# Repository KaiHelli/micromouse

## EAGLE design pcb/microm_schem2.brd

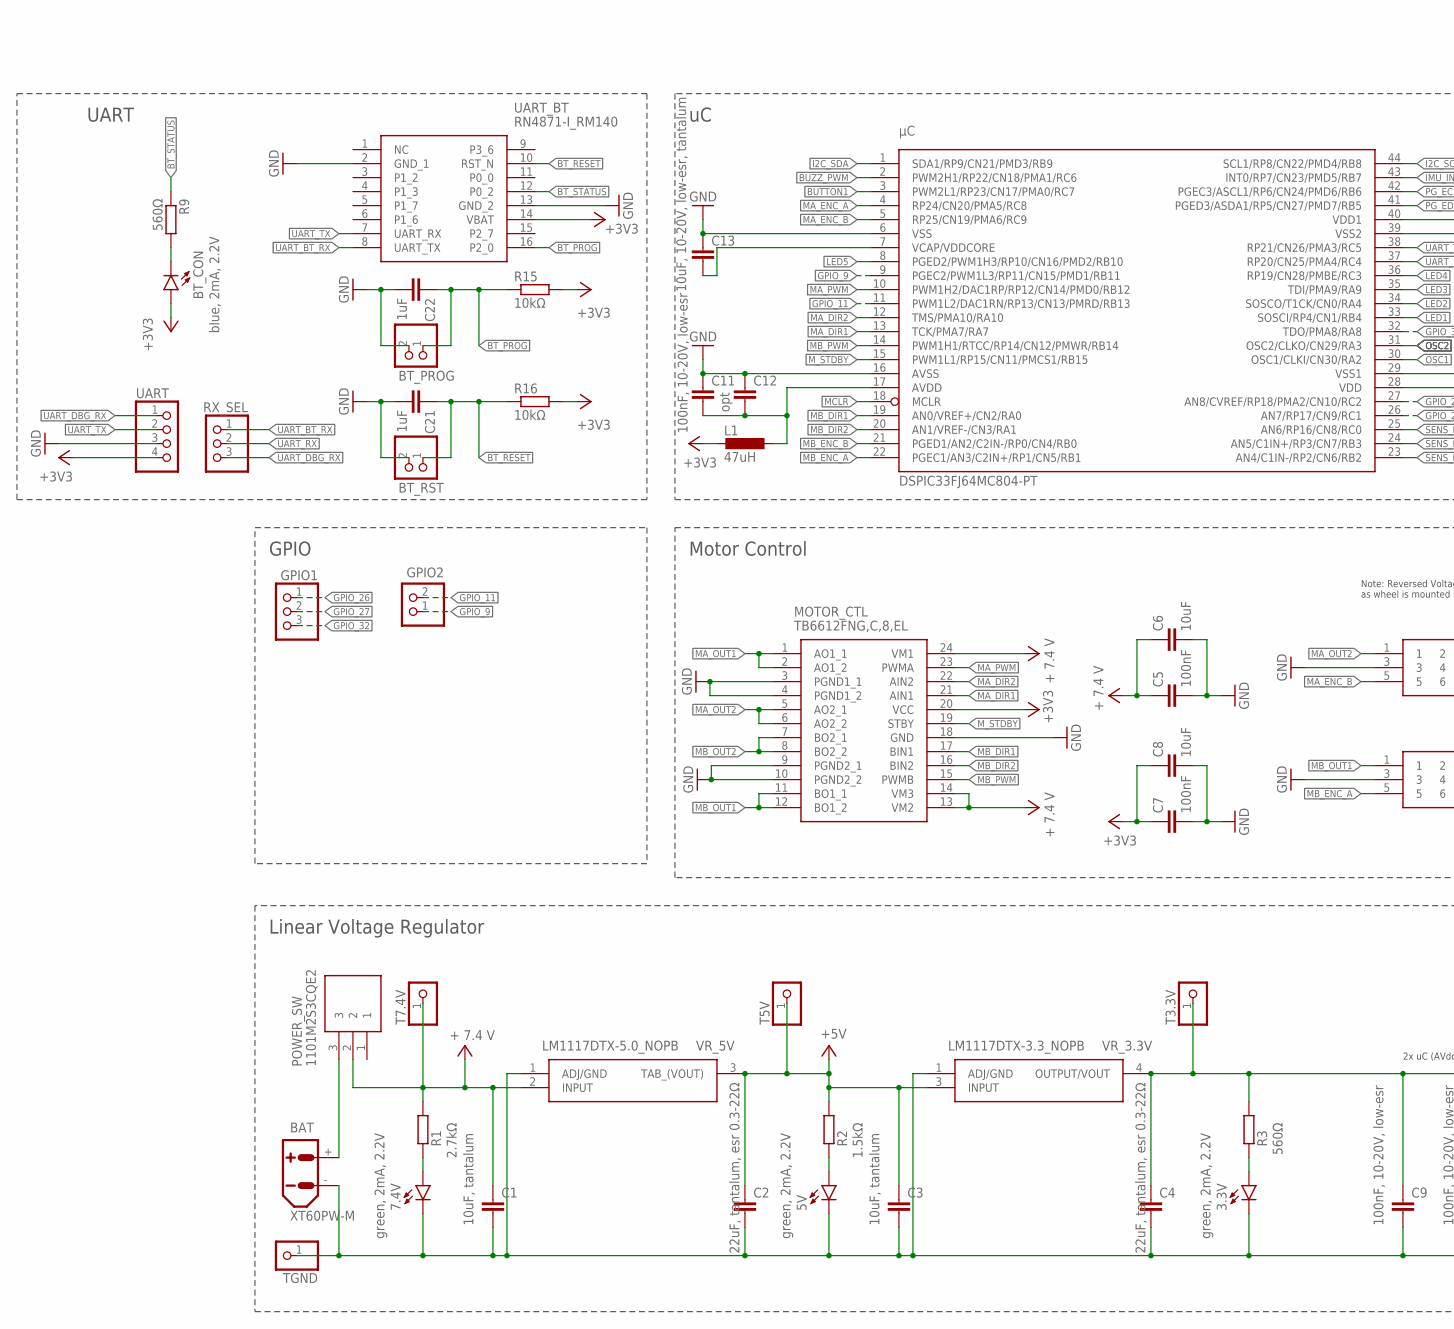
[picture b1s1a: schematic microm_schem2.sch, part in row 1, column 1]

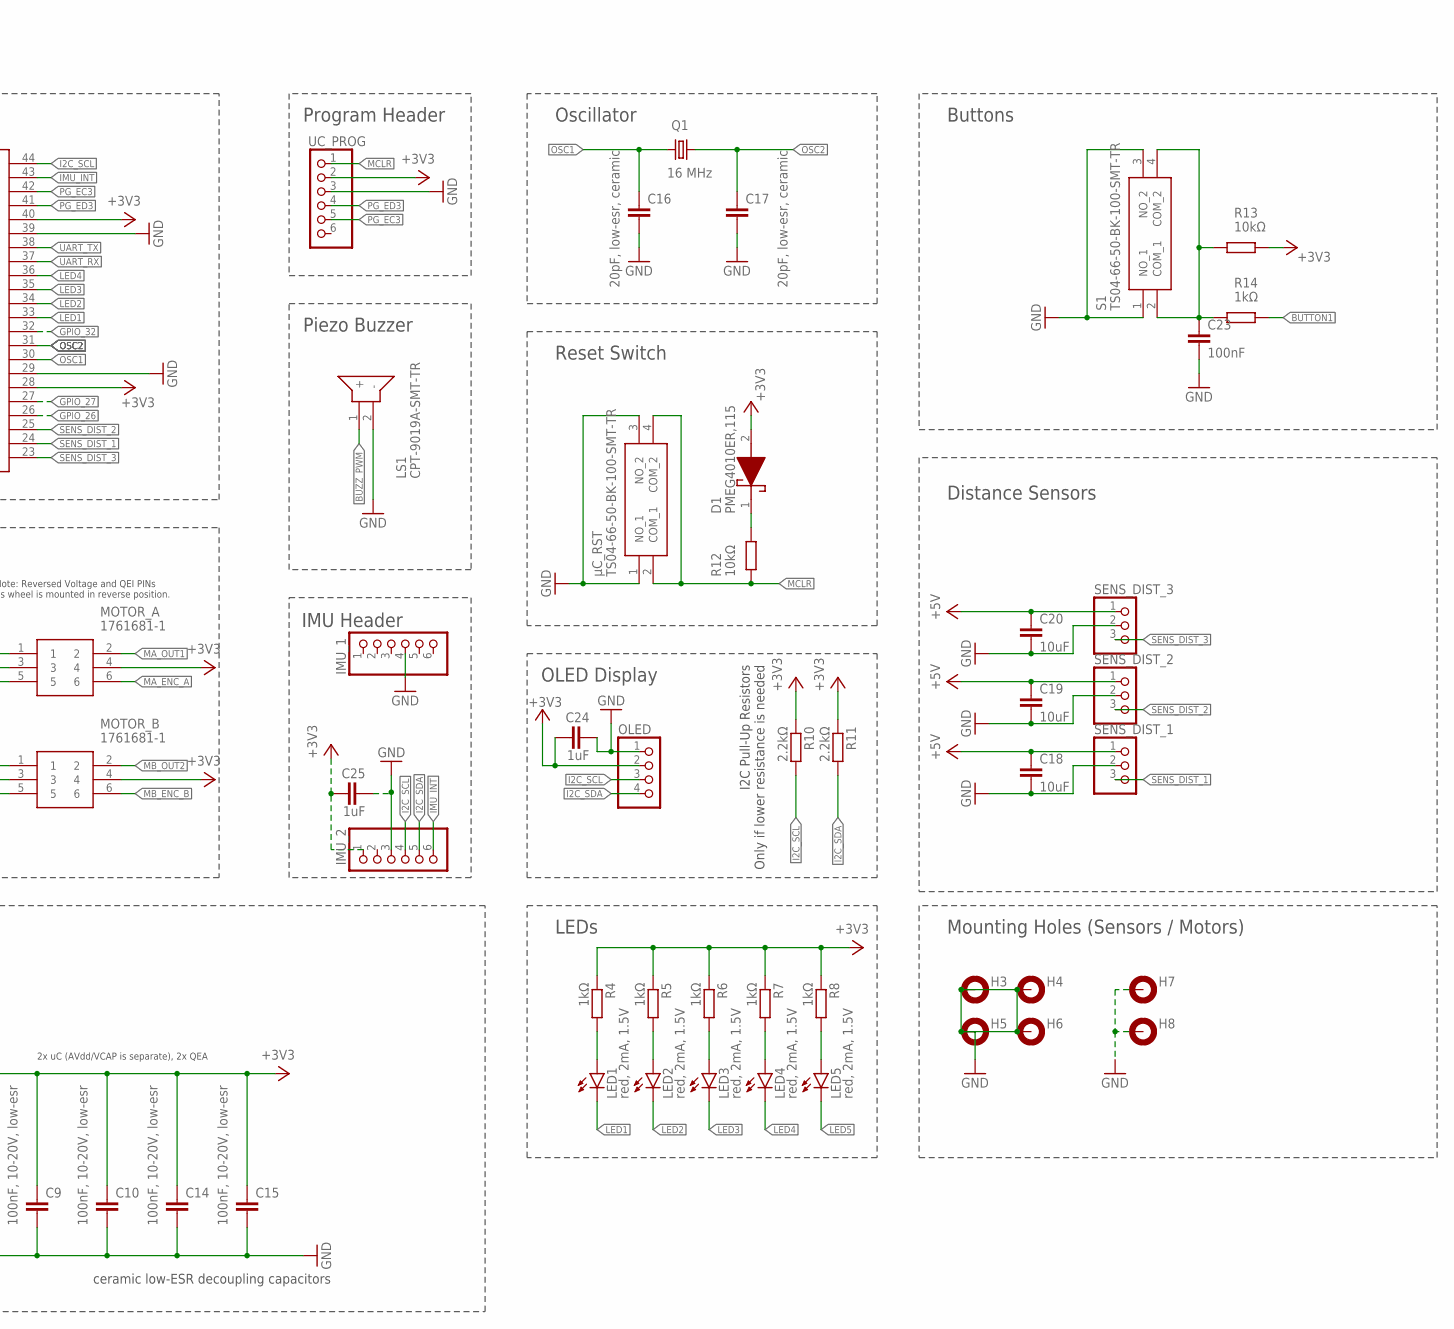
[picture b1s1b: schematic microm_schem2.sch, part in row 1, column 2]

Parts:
3.3V, 5V, 7.4V: green, 2mA, 2.2V; CHIP-LED0805
BAT: XT60PW-M
BT_CON: blue, 2mA, 2.2V; CHIP-LED0805
BT_PROG: PINHD-1X2; 1X02
BT_RST: PINHD-1X2; 1X02
C1, C3: 10uF, tantalum; C0805
C2, C4: 22uF, tantalum, esr 0.3-22Ω; C0805
C5, C7, C23: 100nF; C0805
C6, C8, C18, C19, C20: 10uF; C0805
C9, C10, C11, C14, C15: 100nF, 10-20V, low-esr; C0805
C12: opt; C0805
C13: 10uF, 10-20V, low-esr, tantalum; C0805
C16, C17: 20pF, low-esr, ceramic; C0805
C21, C22, C24, C25: 1uF; C0805
D1: PMEG4010ER,115; PMEG4010ER115
GPIO1: PINHD-1X3; 1X03
GPIO2: PINHD-1X2; 1X02
H3, H4, H5, H6, H7, H8: MOUNT-PAD-ROUND2.8; 2,8-PAD
IMU_1, IMU_2: PINHD-1X6; 1X06
L1: 47uH; L1812
LED1, LED2, LED3, LED4, LED5: red, 2mA, 1.5V; CHIPLED_0805
LS1: CPT-9019A-SMT-TR; CPT9019ASMTTR
MOTOR_A: 1761681-1; SHDR6W67P254_2X3_1524X916X922P
MOTOR_B: 1761681-1; SHDR6W67P254_2X3_1524X916X922P
MOTOR_CTL: TB6612FNG,C,8,EL; SOP65P760X160-24N
OLED: PINHD-1X4; 1X04
POWER_SW: 1101M2S3CQE2; 1000-SERIES(SPDT)
Q1: 16 MHz; HC49/S
R1: 2.7kΩ; R0805
R2: 1.5kΩ; R0805
R3, R9: 560Ω; R0805
R4, R5, R6, R7, R8, R14: 1kΩ; R0805
R10, R11: 2.2kΩ; R0805
R12, R13, R15, R16: 10kΩ; R0805
RX_SEL: PINHD-1X3; 1X03
S1: TS04-66-50-BK-100-SMT-TR; TS046650BK100SMTTR
SENS_DIST_1, SENS_DIST_2, SENS_DIST_3: PINHD-1X3; 1X03
T3.3V, T5V, T7.4V: PINHD-1X1; 1X01
TGND: PINHD-1X1; 1X01
UART: PINHD-1X4; 1X04
UART_BT: RN4871-I_RM140; RN4871IRM140
UC_PROG: PINHD-1X6; 1X06
VR_3.3V: LM1117DTX-3.3_NOPB; LM1117DTX33NOPB
VR_5V: LM1117DTX-5.0_NOPB; LM78M05CDT
µC_RST: TS04-66-50-BK-100-SMT-TR; TS046650BK100SMTTR
μC: DSPIC33FJ64MC804-PT; TQFP44

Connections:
+3V3: BT_CON.A, C4.1, C7.1, C8.1, C9.1, C10.1, C14.1, C15.1, C24.1, C25.1, D1.2 (A), IMU_2.1, L1.2, MOTOR_A.4, MOTOR_B.4, MOTOR_CTL.20 (VCC), OLED.2, R3.1, R4.1, R5.1, R6.1, R7.1, R8.1, R10.1, R11.1, R13.2, R15.2, R16.2, T3.3V.1, UART.4, UART_BT.14 (VBAT), UC_PROG.2, VR_3.3V.4 (OUTPUT/VOUT), μC.28 (VDD), μC.40 (VDD1)
+5V: C2.1, C3.1, C18.1, C19.1, C20.1, R2.1, SENS_DIST_1.1, SENS_DIST_2.1, SENS_DIST_3.1, T5V.1, VR_3.3V.3 (INPUT), VR_5V.3 (TAB_(VOUT))
+7V4: C1.1, C5.1, C6.1, MOTOR_CTL.13 (VM2), MOTOR_CTL.14 (VM3), MOTOR_CTL.24 (VM1), POWER_SW.2, R1.1, T7.4V.1, VR_5V.2 (INPUT)
BT_PROG: BT_PROG.1, C22.1, R15.1, UART_BT.16 (P2_0)
BT_RESET: BT_RST.1, C21.1, R16.1, UART_BT.10 (RST_N)
BT_STATUS: R9.1, UART_BT.12 (P0_2)
BUTTON1: R14.2, μC.3 (PWM2L1/RP23/CN17/PMA0/RC7)
BUZZ_PWM: LS1.1 (+), μC.2 (PWM2H1/RP22/CN18/PMA1/RC6)
GND: 3.3V.C, 5V.C, 7.4V.C, BAT.-, BT_PROG.2, BT_RST.2, C1.2, C2.2, C3.2, C4.2, C5.2, C6.2, C7.2, C8.2, C9.2, C10.2, C11.1, C12.1, C13.1, C14.2, C15.2, C16.2, C17.2, C18.2, C19.2, C20.2, C21.2, C22.2, C23.2, C24.2, C25.2, H3.B2,8, H4.B2,8, H5.B2,8, H6.B2,8, H7.B2,8, H8.B2,8, IMU_1.4, IMU_2.3, LS1.2 (-), MOTOR_A.3, MOTOR_B.3, MOTOR_CTL.3 (PGND1_1), MOTOR_CTL.4 (PGND1_2), MOTOR_CTL.9 (PGND2_1), MOTOR_CTL.10 (PGND2_2), MOTOR_CTL.18 (GND), OLED.1, S1.1 (NO_1), S1.3 (NO_2), SENS_DIST_1.2, SENS_DIST_2.2, SENS_DIST_3.2, TGND.1, UART.3, UART_BT.2 (GND_1), UART_BT.13 (GND_2), UC_PROG.3, VR_3.3V.1 (ADJ/GND), VR_5V.1 (ADJ/GND), µC_RST.1 (NO_1), µC_RST.3 (NO_2), μC.6 (VSS), μC.16 (AVSS), μC.29 (VSS1), μC.39 (VSS2)
GPIO_9: GPIO2.1, μC.9 (PGEC2/PWM1L3/RP11/CN15/PMD1/RB11)
GPIO_11: GPIO2.2, μC.11 (PWM1L2/DAC1RN/RP13/CN13/PMRD/RB13)
GPIO_26: GPIO1.1, μC.26 (AN7/RP17/CN9/RC1)
GPIO_27: GPIO1.2, μC.27 (AN8/CVREF/RP18/PMA2/CN10/RC2)
GPIO_32: GPIO1.3, μC.32 (TDO/PMA8/RA8)
I2C_SCL: IMU_2.4, OLED.3, R10.2, μC.44 (SCL1/RP8/CN22/PMD4/RB8)
I2C_SDA: IMU_2.5, OLED.4, R11.2, μC.1 (SDA1/RP9/CN21/PMD3/RB9)
IMU_INT: IMU_2.6, μC.43 (INT0/RP7/CN23/PMD5/RB7)
LED1: LED1.C, μC.33 (SOSCI/RP4/CN1/RB4)
LED2: LED2.C, μC.34 (SOSCO/T1CK/CN0/RA4)
LED3: LED3.C, μC.35 (TDI/PMA9/RA9)
LED4: LED4.C, μC.36 (RP19/CN28/PMBE/RC3)
LED5: LED5.C, μC.8 (PGED2/PWM1H3/RP10/CN16/PMD2/RB10)
MA_DIR1: MOTOR_CTL.21 (AIN1), μC.13 (TCK/PMA7/RA7)
MA_DIR2: MOTOR_CTL.22 (AIN2), μC.12 (TMS/PMA10/RA10)
MA_ENC_A: MOTOR_A.6, μC.4 (RP24/CN20/PMA5/RC8)
MA_ENC_B: MOTOR_A.5, μC.5 (RP25/CN19/PMA6/RC9)
MA_OUT1: MOTOR_A.2, MOTOR_CTL.1 (AO1_1), MOTOR_CTL.2 (AO1_2)
MA_OUT2: MOTOR_A.1, MOTOR_CTL.5 (AO2_1), MOTOR_CTL.6 (AO2_2)
MA_PWM: MOTOR_CTL.23 (PWMA), μC.10 (PWM1H2/DAC1RP/RP12/CN14/PMD0/RB12)
MB_DIR1: MOTOR_CTL.17 (BIN1), μC.19 (AN0/VREF+/CN2/RA0)
MB_DIR2: MOTOR_CTL.16 (BIN2), μC.20 (AN1/VREF-/CN3/RA1)
MB_ENC_A: MOTOR_B.5, μC.22 (PGEC1/AN3/C2IN+/RP1/CN5/RB1)
MB_ENC_B: MOTOR_B.6, μC.21 (PGED1/AN2/C2IN-/RP0/CN4/RB0)
MB_OUT1: MOTOR_B.1, MOTOR_CTL.11 (BO1_1), MOTOR_CTL.12 (BO1_2)
MB_OUT2: MOTOR_B.2, MOTOR_CTL.7 (BO2_1), MOTOR_CTL.8 (BO2_2)
MB_PWM: MOTOR_CTL.15 (PWMB), μC.14 (PWM1H1/RTCC/RP14/CN12/PMWR/RB14)
MCLR: R12.1, UC_PROG.1, µC_RST.2 (COM_1), µC_RST.4 (COM_2), μC.18 (MCLR)
M_STDBY: MOTOR_CTL.19 (STBY), μC.15 (PWM1L1/RP15/CN11/PMCS1/RB15)
unnamed: BT_CON.C, R9.2
unnamed: BAT.+, POWER_SW.3
unnamed: LED1.A, R4.2
unnamed: 7.4V.A, R1.2
unnamed: C11.2, C12.2, L1.1, μC.17 (AVDD)
unnamed: C23.1, R13.1, R14.1, S1.2 (COM_1), S1.4 (COM_2)
unnamed: D1.1 (K), R12.2
unnamed: LED2.A, R5.2
unnamed: 5V.A, R2.2
unnamed: 3.3V.A, R3.2
unnamed: LED3.A, R6.2
unnamed: LED4.A, R7.2
unnamed: LED5.A, R8.2
OSC1: C16.1, Q1.1, μC.30 (OSC1/CLKI/CN30/RA2)
OSC2: C17.1, Q1.2, μC.31 (OSC2/CLKO/CN29/RA3)
PG_EC3: UC_PROG.5, μC.42 (PGEC3/ASCL1/RP6/CN24/PMD6/RB6)
PG_ED3: UC_PROG.4, μC.41 (PGED3/ASDA1/RP5/CN27/PMD7/RB5)
SENS_DIST_1: SENS_DIST_1.3, μC.24 (AN5/C1IN+/RP3/CN7/RB3)
SENS_DIST_2: SENS_DIST_2.3, μC.25 (AN6/RP16/CN8/RC0)
SENS_DIST_3: SENS_DIST_3.3, μC.23 (AN4/C1IN-/RP2/CN6/RB2)
UART_BT_RX: RX_SEL.1, UART_BT.8 (UART_TX)
UART_DBG_RX: RX_SEL.3, UART.1
UART_RX: RX_SEL.2, μC.37 (RP20/CN25/PMA4/RC4)
UART_TX: UART.2, UART_BT.7 (UART_RX), μC.38 (RP21/CN26/PMA3/RC5)
VCAP/VDDCORE: C13.2, μC.7 (VCAP/VDDCORE)

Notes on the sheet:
Oscillator
Program Header
Reset Switch
Distance Sensors
Motor Control
ceramic low-ESR decoupling capacitors
Linear Voltage Regulator
LEDs
Buttons
Piezo Buzzer
IMU Header
UART
2x uC (AVdd/VCAP is separate), 2x QEA
Note: Reversed Voltage and QEI PINs as wheel is mounted in reverse position.
I2C Pull-Up Resistors Only if lower resistance is needed
Mounting Holes (Sensors / Motors)
OLED Display
GPIO

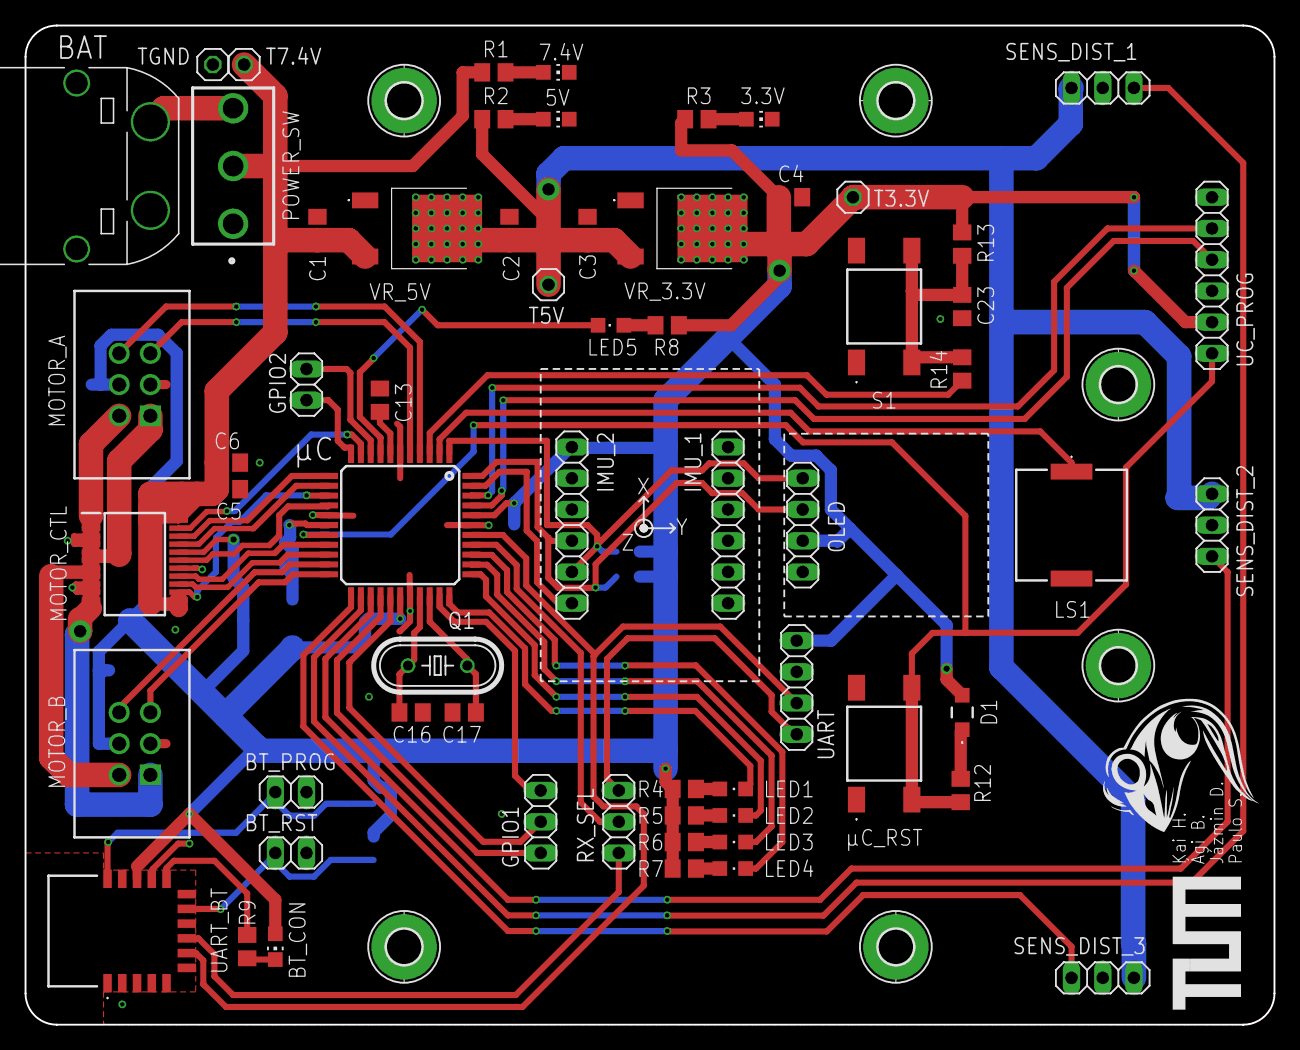
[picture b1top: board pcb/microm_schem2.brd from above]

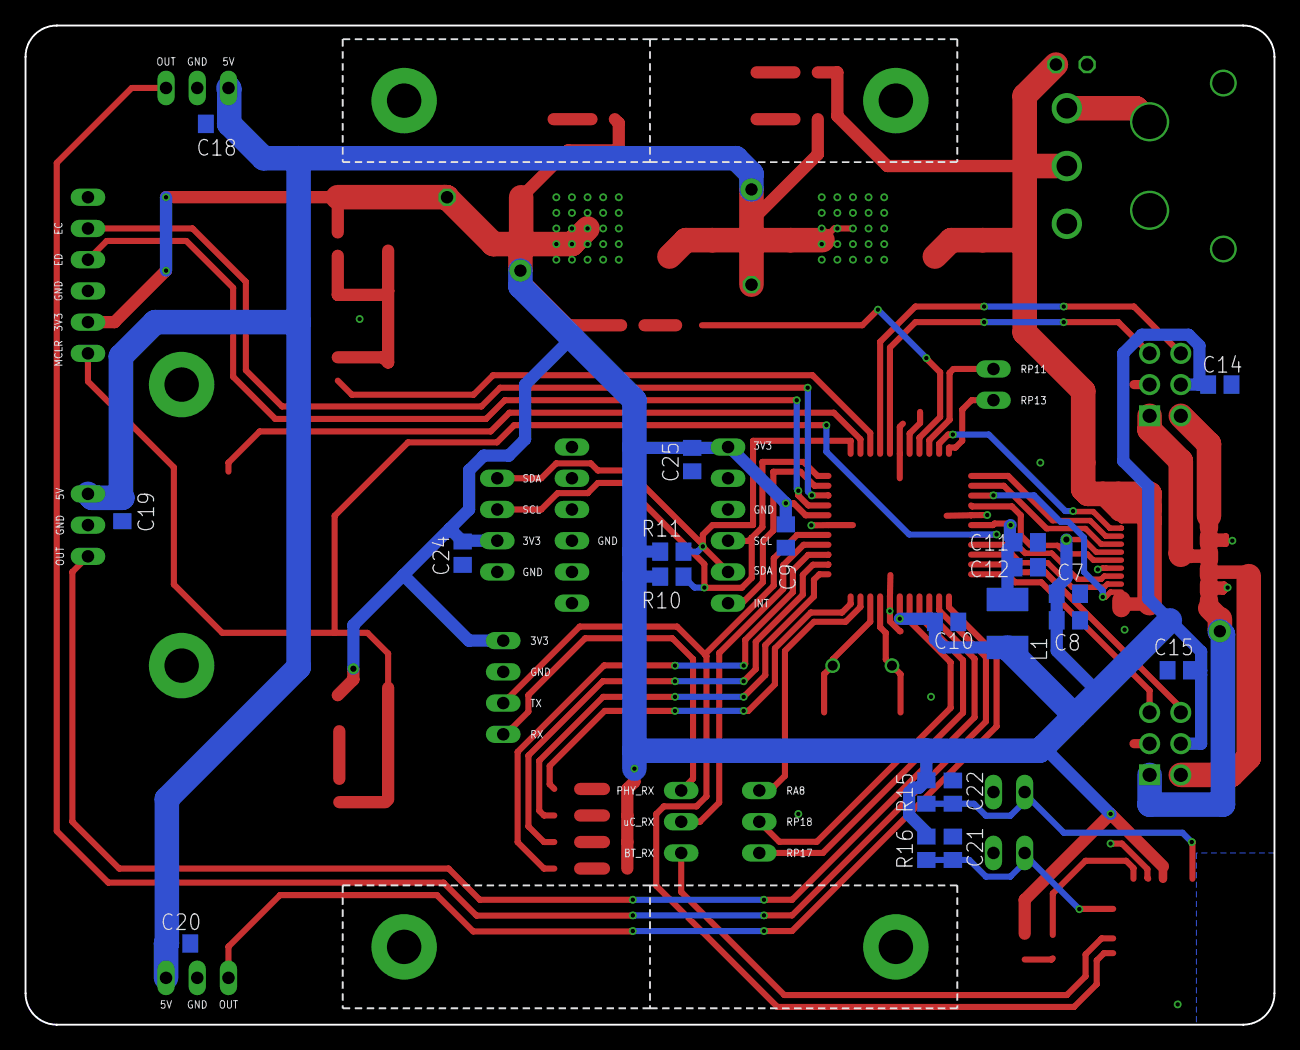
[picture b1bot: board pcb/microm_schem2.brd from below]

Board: 2 copper layers, 101.6 x 81.3 mm, 88 parts (20 on the bottom side), 63 nets.

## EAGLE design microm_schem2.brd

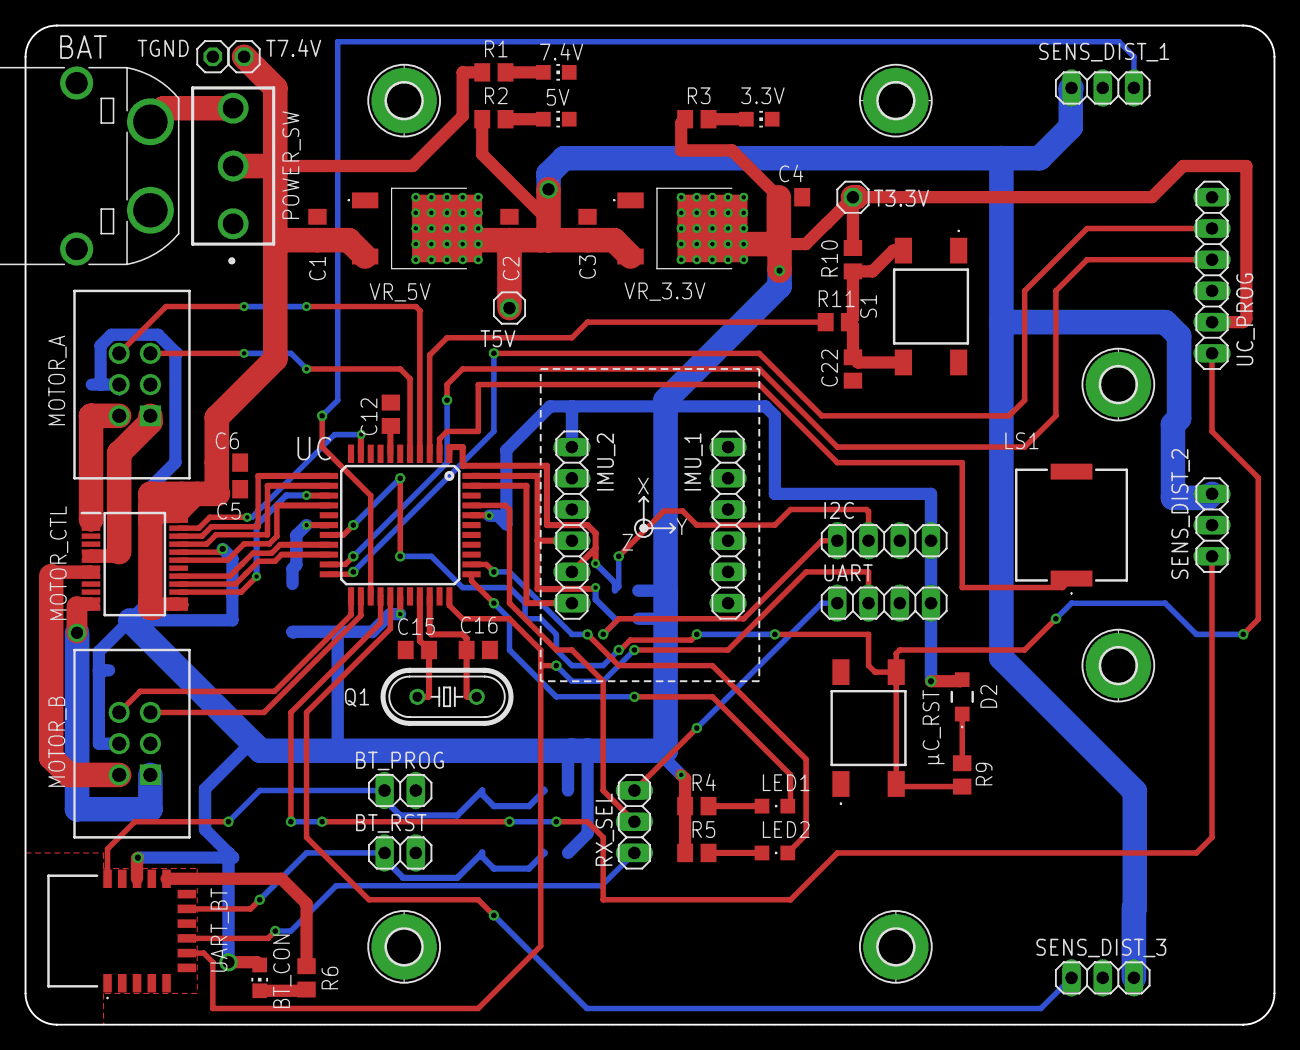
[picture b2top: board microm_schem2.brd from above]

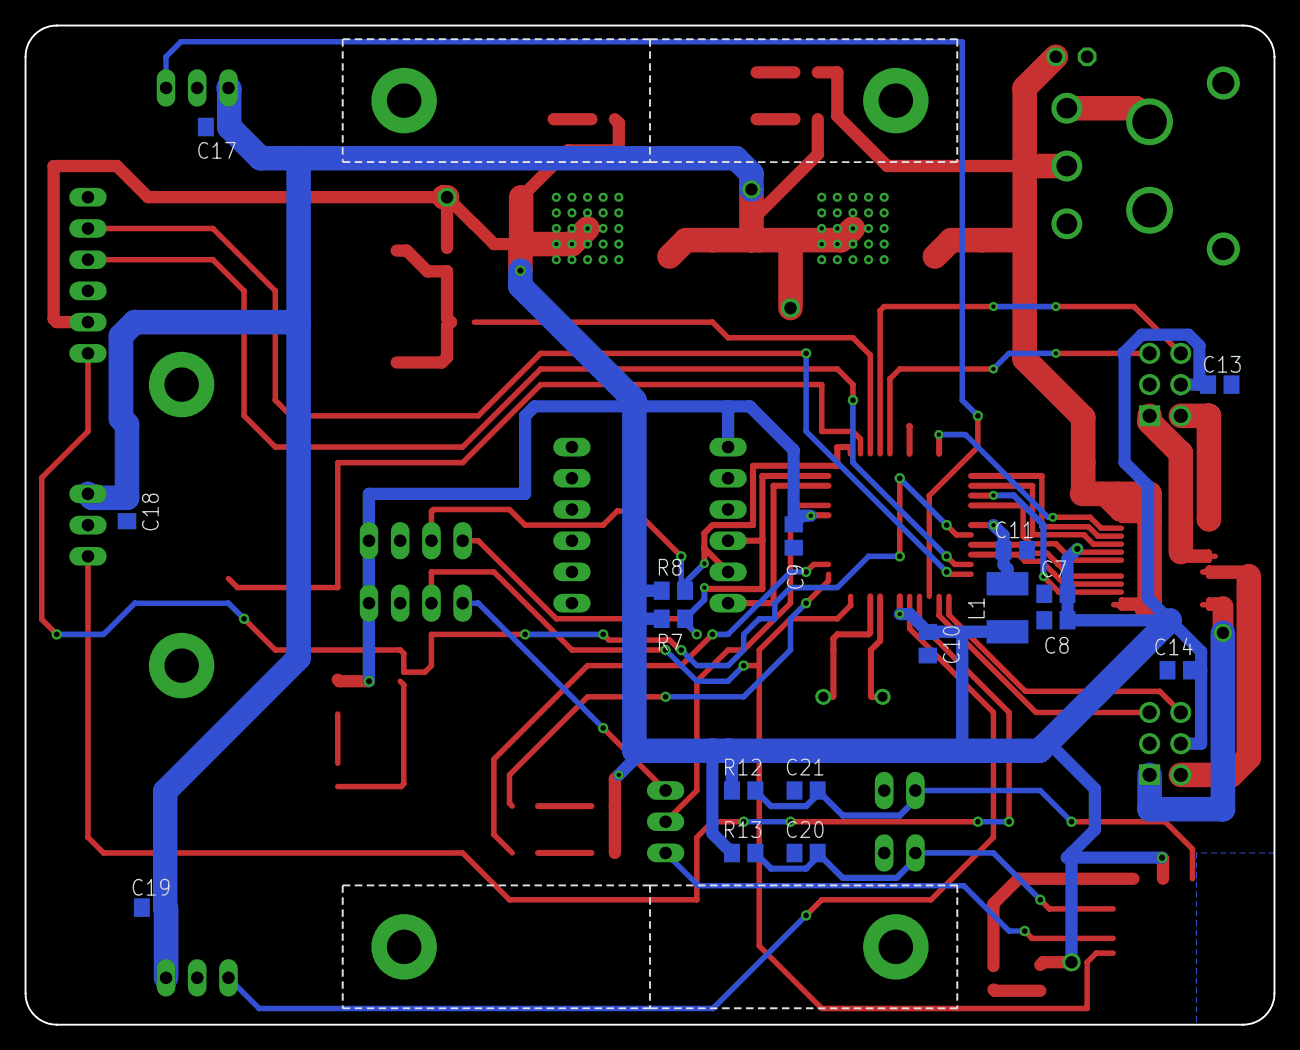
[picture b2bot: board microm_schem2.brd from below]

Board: 2 copper layers, 101.6 x 81.3 mm, 77 parts (17 on the bottom side), 52 nets.

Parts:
3.3V, 5V, 7.4V: green, 2mA, 3V; CHIP-LED0805
BAT: XT60PW-M
BT_CON: blue, 2mA, 3V; CHIP-LED0805
BT_PROG: 1X02
BT_RST: 1X02
C1, C3: 10uF, tantalum; C0805
C2, C4: 22uF, tantalum, esr 0.3-22Ω; C0805
C5, C7, C22: 100nF; C0805
C6, C8: 10uF; C0805
C9, C10, C11, C13, C14: 100nF, 10-20V, low-esr; C0805
C12: 10uF, 10-20V, low-esr; C0805
C15, C16: 20pF, low-esr, ceramic; C0805
C17, C18, C19: 10 uF; C0805
C20, C21: 1uF; C0805
D2: PMEG4010ER,115; PMEG4010ER115
H3, H4, H5, H6, H7, H8: MOUNT-PAD-ROUND2.8; 2,8-PAD
I2C: 1X04
IMU_1, IMU_2: 1X06
L1: 47uH; L1812
LED1, LED2: red, 2mA, 2.1V; CHIPLED_0805
LS1: CPT-9019A-SMT-TR; CPT9019ASMTTR
MOTOR_A: 1761681-1; SHDR6W67P254_2X3_1524X916X922P
MOTOR_B: 1761681-1; SHDR6W67P254_2X3_1524X916X922P
MOTOR_CTL: TB6612FNG,C,8,EL; SOP65P760X160-24N
POWER_SW: 1101M2S3CQE2; 1000-SERIES(SPDT)
Q1: 16 MHz; HC49/S
R1: 2.7kΩ; R0805
R2: 1.2kΩ; R0805
R3, R6: 180Ω; R0805
R4, R5: 680Ω; R0805
R7, R8: 2.2kΩ; R0805
R9, R10, R12, R13: 10kΩ; R0805
R11: 1kΩ; R0805
RX_SEL: 1X03
S1: TS04-66-50-BK-100-SMT-TR; TS046650BK100SMTTR
SENS_DIST_1, SENS_DIST_2, SENS_DIST_3: 1X03
T3.3V, T5V, T7.4V: 1X01
TGND: 1X01
UART: 1X04
UART_BT: RN4871-I_RM140; RN4871IRM140
UC: DSPIC33FJ64MC804-PT; TQFP44
UC_PROG: 1X06
VR_3.3V: LM1117DTX-3.3_NOPB; LM1117DTX33NOPB
VR_5V: LM1117DTX-5.0_NOPB; LM78M05CDT
µC_RST: TS04-66-50-BK-100-SMT-TR; TS046650BK100SMTTR

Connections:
+3V3: BT_CON.A, C4.1, C7.1, C8.1, C9.1, C10.1, C13.1, C14.1, D2.2, I2C.4, IMU_2.1, L1.2, MOTOR_A.4, MOTOR_B.4, MOTOR_CTL.20, R3.1, R4.1, R5.1, R7.1, R8.1, R10.2, R12.2, R13.2, T3.3V.1, UART.4, UART_BT.14, UC.28, UC.40, UC_PROG.2, VR_3.3V.4
+5V: C2.1, C3.1, C17.1, C18.1, C19.1, R2.1, SENS_DIST_1.1, SENS_DIST_2.1, SENS_DIST_3.1, T5V.1, VR_3.3V.3, VR_5V.3
+7V4: C1.1, C5.1, C6.1, MOTOR_CTL.13, MOTOR_CTL.14, MOTOR_CTL.24, POWER_SW.2, R1.1, T7.4V.1, VR_5V.2
BT_PROG: BT_PROG.1, C21.1, R12.1, UART_BT.16
BT_RESET: BT_RST.1, C20.1, R13.1, UART_BT.10
BT_STATUS: R6.1, UART_BT.12
BUTTON1: R11.2, UC.3
BUZZ_PWM: LS1.1, UC.2
GND: 3.3V.C, 5V.C, 7.4V.C, BAT.-, BT_PROG.2, BT_RST.2, C1.2, C2.2, C3.2, C4.2, C5.2, C6.2, C7.2, C8.2, C9.2, C10.2, C11.1, C12.1, C13.2, C14.2, C15.2, C16.2, C17.2, C18.2, C19.2, C20.2, C21.2, C22.2, H3.B2,8, H4.B2,8, H5.B2,8, H6.B2,8, H7.B2,8, H8.B2,8, I2C.3, IMU_1.4, IMU_2.3, LS1.2, MOTOR_A.3, MOTOR_B.3, MOTOR_CTL.3, MOTOR_CTL.4, MOTOR_CTL.9, MOTOR_CTL.10, MOTOR_CTL.18, S1.1, S1.3, SENS_DIST_1.2, SENS_DIST_2.2, SENS_DIST_3.2, TGND.1, UART.3, UART_BT.2, UART_BT.13, UC.6, UC.16, UC.29, UC.39, UC_PROG.3, VR_3.3V.1, VR_5V.1, µC_RST.1, µC_RST.3
I2C_SCL: I2C.1, IMU_2.4, R7.2, UC.44
I2C_SDA: I2C.2, IMU_2.5, R8.2, UC.1
IMU_INT: IMU_2.6, UC.43
LED1: LED1.C, UC.34
LED2: LED2.C, UC.35
MA_DIR1: MOTOR_CTL.21, UC.13
MA_DIR2: MOTOR_CTL.22, UC.12
MA_ENC_A: MOTOR_A.6, UC.4
MA_ENC_B: MOTOR_A.5, UC.5
MA_OUT1: MOTOR_A.2, MOTOR_CTL.1, MOTOR_CTL.2
MA_OUT2: MOTOR_A.1, MOTOR_CTL.5, MOTOR_CTL.6
MA_PWM: MOTOR_CTL.23, UC.10
MB_DIR1: MOTOR_CTL.17, UC.19
MB_DIR2: MOTOR_CTL.16, UC.20
MB_ENC_A: MOTOR_B.5, UC.24
MB_ENC_B: MOTOR_B.6, UC.23
MB_OUT1: MOTOR_B.1, MOTOR_CTL.11, MOTOR_CTL.12
MB_OUT2: MOTOR_B.2, MOTOR_CTL.7, MOTOR_CTL.8
MB_PWM: MOTOR_CTL.15, UC.14
MCLR: R9.1, UC.18, UC_PROG.1, µC_RST.2, µC_RST.4
M_STDBY: MOTOR_CTL.19, UC.15
unnamed: BT_CON.C, R6.2
unnamed: BAT.+, POWER_SW.3
unnamed: LED1.A, R4.2
unnamed: 7.4V.A, R1.2
unnamed: C11.2, L1.1, UC.17
unnamed: C22.1, R10.1, R11.1, S1.2, S1.4
unnamed: D2.1, R9.2
unnamed: LED2.A, R5.2
unnamed: 5V.A, R2.2
unnamed: 3.3V.A, R3.2
OSC1: C15.1, Q1.1, UC.30
OSC2: C16.1, Q1.2, UC.31
PG_EC1: UC.22, UC_PROG.5
PG_ED1: UC.21, UC_PROG.4
SENS_DIST_1: SENS_DIST_1.3, UC.25
SENS_DIST_2: SENS_DIST_2.3, UC.26
SENS_DIST_3: SENS_DIST_3.3, UC.27
UART_BT_RX: RX_SEL.1, UART_BT.8
UART_DBG_RX: RX_SEL.3, UART.1
UART_RX: RX_SEL.2, UC.41
UART_TX: UART.2, UART_BT.7, UC.33
VCAP/VDDCORE: C12.2, UC.7

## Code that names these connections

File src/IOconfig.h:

#ifndef IOCONFIG_H
#define IOCONFIG_H

#define SW1 !PORTCbits.RC7
#define IMU_INT PORTBbits.RB7

#define MA_DIR1 LATAbits.LATA7
#define MA_DIR2 LATAbits.LATA10
#define MB_DIR1 LATAbits.LATA0
#define MB_DIR2 LATAbits.LATA1

#define MA_PWM_MODULE  1
#define MA_PWM_CHANNEL 2

#define MB_PWM_MODULE  1
#define MB_PWM_CHANNEL 1

#define LED5_PWM_MODULE  1
#define LED5_PWM_CHANNEL 3

#define BUZZ_PWM_MODULE  2
#define BUZZ_PWM_CHANNEL 1

#define M_STDBY LATBbits.LATB15

#define LED1 LATBbits.LATB4
#define LED2 LATAbits.LATA4
#define LED3 LATAbits.LATA9
#define LED4 LATCbits.LATC3
#define LED5 LATBbits.LATB10

#define GPIO09 LATBbits.LATB11
#define GPIO11 LATBbits.LATB12
#define GPIO26 LATCbits.LATC1
#define GPIO27 LATCbits.LATC2
#define GPIO32 LATAbits.LATA8

#define LEDON 0
#define LEDOFF 1

/**
 * @brief Configures all necessary I/O pins and directions.
 * 
 * Sets up the digital/analog configuration for the device pins, and any
 * additional I/O initialization that may be required.
 * NOTE: ADC and PWM setup is done in adc.c and pwm.c
 */
void setupIO();

#endif /* IOCONFIG_H */

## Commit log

2024-12-05 Add my files
2024-12-05 clang-format -i -style=WebKit *.c *.h
2024-12-05 Fix UART issues
2024-12-06 Fix UART transmission issue
2024-12-06 Code formatting
2025-01-17 Added schematics and library parts
    SamacSys_party.lbr must be places placed under your "EAGLE/libraries" folder.
2025-01-17 Add dma and adc code.
2025-01-18 Update schematics and library.
2025-01-19 Add IMU and LCD, complete wiring and clean up.
2025-01-19 Fix led resitors.
2025-01-19 Fix ERC issues and add mounting pads.
2025-01-20 Add first version of the PCB.
2025-01-20 Hide ground airwires.
2025-01-23 Add changes from meeting today.
2025-01-29 Update schematic.
2025-01-31 WIP: Trace the airwires
2025-02-01 Improve 3.3V routing.
2025-02-04 Finished board
2025-02-05 Add most recent board version
2025-02-05 Add exported shopping cart of parts
2025-02-05 Fix overlapping uart and sensor routes
2025-02-05 Move pcb files into subdirectory
2025-02-06 Optimizations on pcb, unify via sizes and trace widths.
2025-02-08 More wiring optimizations.
2025-02-08 Few more optimizations.
2025-02-09 Fix DRC issues.
2025-02-09 Add Beta Layout DRU files.
2025-02-10 Further refinements.
2025-02-10 Minor adjustments.
2025-02-10 Add GPIO header for remaining pins.
2025-02-10 Finalize traces.
2025-02-10 Add TUM logo and update values.
2025-02-10 Add mouse logo.
2025-02-11 Add pin descriptions.
2025-02-11 Fix LED resistors.
2025-02-12 Add updated parts list.
2025-02-12 Final fixes.
2025-02-27 Adapt source code for pcb pin mapping.
2025-02-28 Add I2C communication code (untested).
2025-03-11 WIP: Add code to setup IMU.
2025-03-13 Add a buffer for async UART and I2C to hold multiple transactions.
2025-03-13 Minor fix in priority.
2025-03-13 WIP: Read measurements from imu.
2025-03-14 WIP: Initial LCD testing code.
2025-03-16 Minor fixes and add code to support RTTTL songs on buzzer.
2025-03-17 Add first verion of high level maze solving algorithm and PID control
2025-03-17 Fix main IMU bugs.
2025-03-18 Add imu gyroscope calibration on startup.
2025-03-20 Code restructuring and adding the headers of code still needed.
2025-03-20 Add docstrings to header files.
2025-03-20 Add support for timers 4 and 5.
2025-03-25 Add option to init timer in us instead of ms.
2025-03-26 Added implementation for sensors and a first draft for the motors
2025-03-26 Add global timer to track time since startup.
2025-03-26 Change to 16 bit sensor reading and recalibrate sensor
2025-03-26 added scripts and sensor datsa
2025-03-26 Fix global timers
2025-03-26 Add motor states turn left, right
2025-03-26 Add functions to change the motors direction individually
2025-03-26 Implemented steering
2025-03-26 Finish missing timer and switch callback implementations, add basic oled
    functions.
2025-03-27 Fix timers.
2025-03-27 Fix i2c status.
2025-03-27 Change timer to use for rtttl to be configurable.
2025-03-27 Add PID control
2025-03-27 Change motor standby handling
2025-03-27 Add higher level logic
2025-03-28 WIP: Fix oled interface
2025-03-28 Refactor pwm functions to use integer arithmetic.
2025-03-28 Add pid implementation based on integer arithmetic.
2025-03-28 Fix oled issues.
2025-03-28 Minor optimization.
2025-03-28 Add estimation of time it takes to write the display buffer.
2025-03-30 Add code to calibrate accelerometer.
2025-03-30 WIP: Add odometry tracking.
2025-03-30 WIP: Improve odometry. Add code to turn a certain amount of degrees.
2025-03-31 Add configuration.
2025-04-15 Add motor encoder changes and fixes.
2025-04-15 added maze lcd visualisation
2025-04-18 Improve odometry using a complementary filter.
2025-04-18 Add velocity and position estimates to odometry.
2025-04-18 small tweak lcd
2025-04-18 fixed visualisation of maze
2025-04-18 Add pids to control wheel speeds.
2025-04-19 WIP: Improve movements
2025-04-21 WIP: Improve encoder velocity estimates and movements.
2025-04-22 Improve maze solver
2025-04-22 Add allocation test
2025-04-22 Adjust memory allocation
2025-04-23 commented out rttl to make space for mazesolver and future code
2025-04-23 restructured scripts and img folder
2025-04-25 Refactor imu code to support FIFO readings.
2025-04-25 Fix max dataset bytes
2025-04-25 Fix comment
2025-04-26 WIP: Improve movements and odometry
2025-04-26 WIP: solve the maze and print to oled
2025-04-27 added some delays and first draft of orientation
2025-04-27 Fix higher level logic
2025-04-27 Fix mazesolver path optimization
2025-04-28 added turn orientation
2025-04-28 Change maze solver to absolute turning
2025-04-29 fixed orientation rotation
2025-04-29 WIP: Add callbacks that execute only every num ticks. Various other
    changes.
2025-05-02 WIP: Change movements to a competitive kinematics control.
2025-05-03 WIP: fix issues in ported mouse control code
2025-05-04 WIP: Try to fix inaccurate distances.
2025-05-04 WIP: First version which runs in the maze. Distances are underestimated.
2025-05-04 Minor fixes.
2025-05-05 WIP: Add better encoder velocity estimat and feedforward term for pid.
2025-05-07 Add first version that is able to solve the maze more consistently.
2025-05-07 Fix compiler warning.
2025-05-07 Fix command limiting
2025-05-07 Add better plotting code.
2025-05-07 Repo cleanup.
2025-05-07 Add calibrate source
2025-05-07 Add readme.
2025-05-07 Cleanup.
